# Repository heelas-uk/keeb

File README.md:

# Keeb
A project for hackclub ~keeb~ forge YSWS 

It's a stenography keyboard. It is custom because my keyboard doesn't have proper n key roll over. This is also my first time in cad and kicad so its bad. 

This is the schematic of what I have made. 

# How to make

1. Acquire the pcb and 3d model of the case in pla (realistically you should use the one with no top since the top plate isn't essential and a pain to print).

3. Acquire other components per bill of materials

4. Soldering fun. Attach the components with lead free solder.

5. Check it works... kinda really important before you put it in a case

6. Build the case with self tapping screws so there is good stability.

7. Flash the firmware by holding bootsel and drag and drop

8. Install plover HID on you device and plugin via usb

9. It should now work. Yay!

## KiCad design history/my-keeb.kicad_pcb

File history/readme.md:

I have quite litterally just uploaded the files as amd when they were added to the histpry repo in kicad

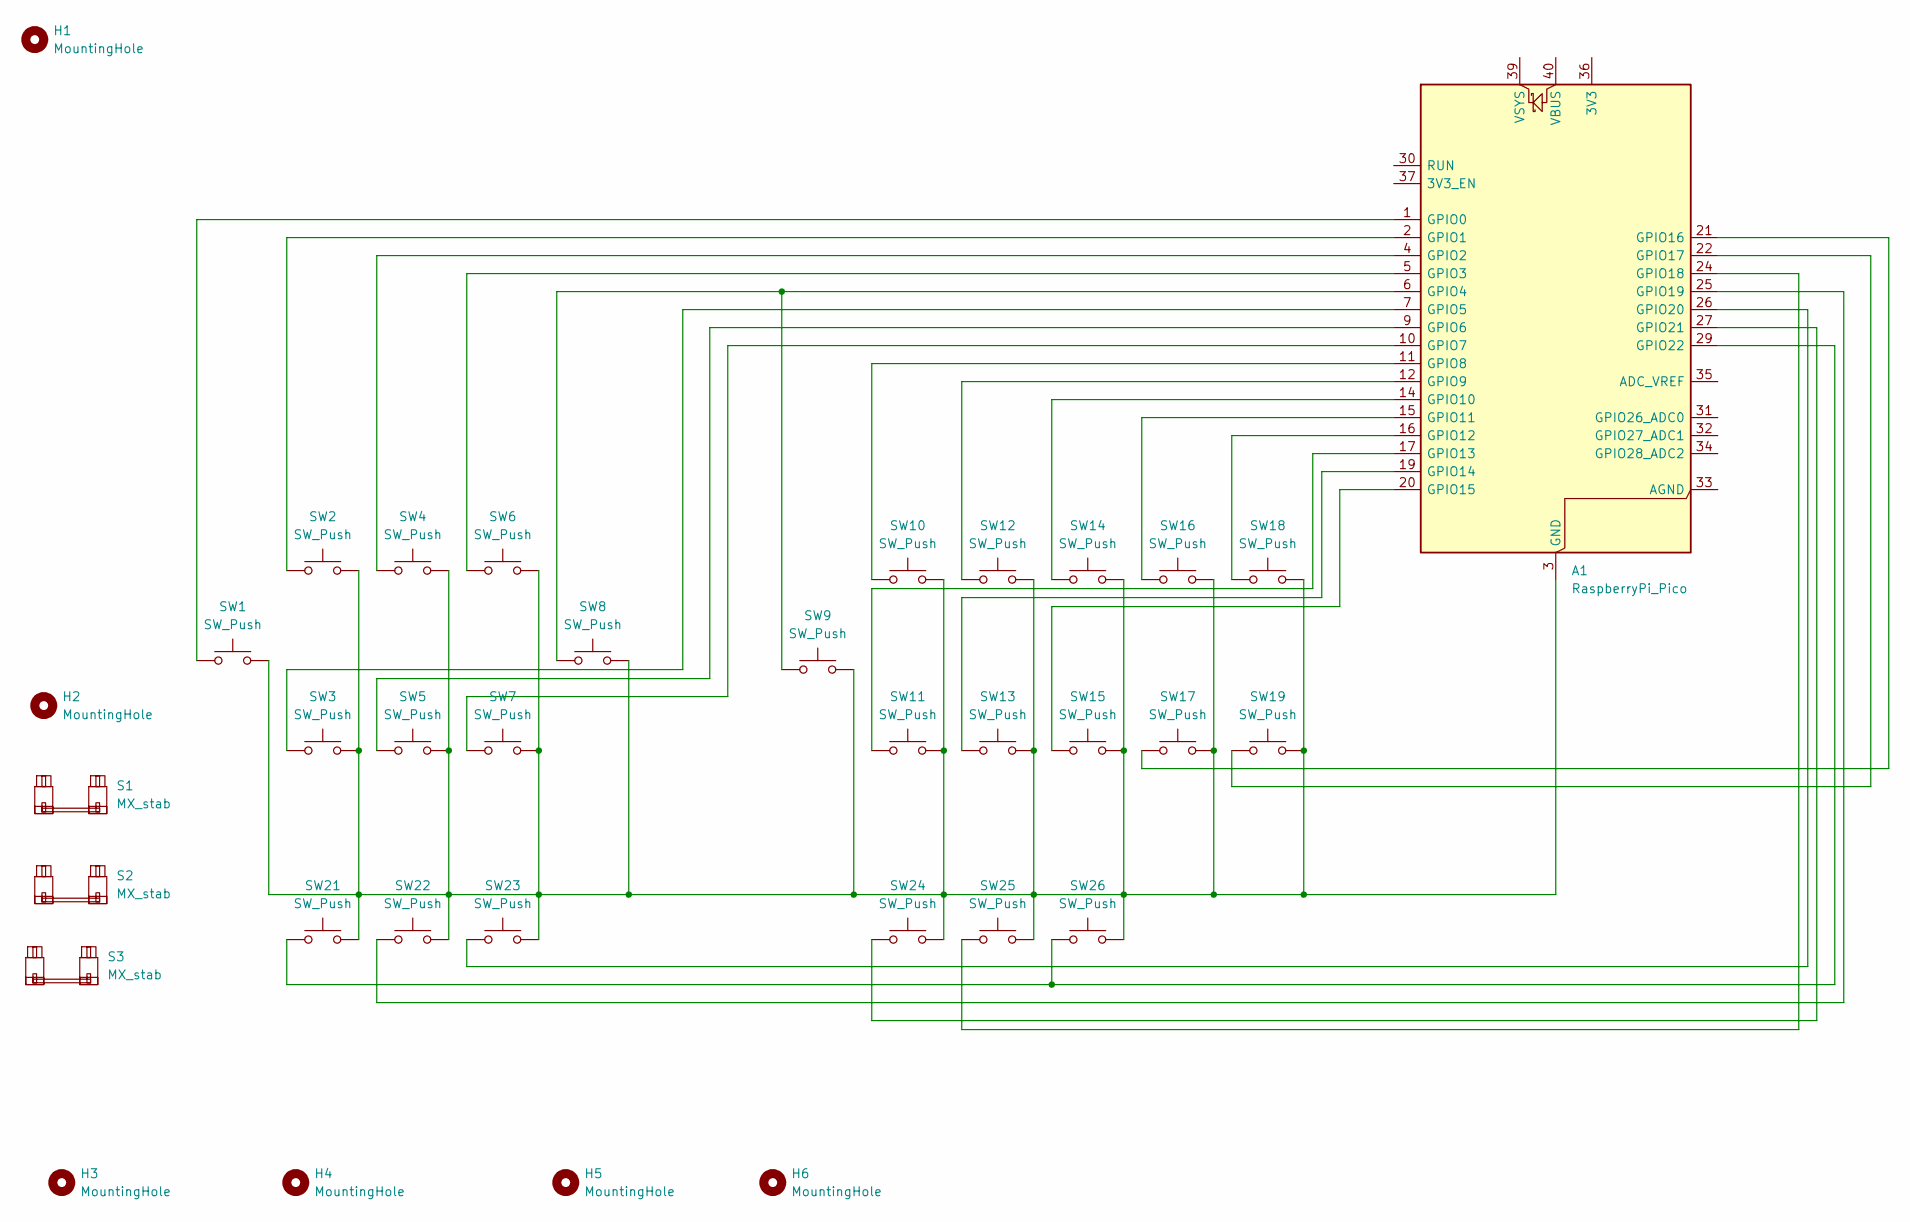
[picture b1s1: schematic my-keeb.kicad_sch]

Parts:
A1: RaspberryPi_Pico; RaspberryPi_Pico_Common_THT
H1, H2, H3, H4, H5, H6: MountingHole; MountingHole_3.2mm_M3
S1, S2, S3: MX_stab; STAB_MX_P_2u
SW1, SW2, SW3, SW4, SW5, SW6, SW7, SW8, SW9, SW10, SW11, SW12, SW13, SW14, SW15, SW16, SW17, SW18, SW19, SW21, SW22, SW23, SW24, SW25, SW26: SW_Push; SW_MX_1u

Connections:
unnamed: A1.3 (GND), A1.8 (GND), A1.13 (GND), A1.18 (GND), A1.23 (GND), A1.28 (GND), A1.38 (GND), SW1.2, SW2.2, SW3.2, SW4.2, SW5.2, SW6.2, SW7.2, SW8.2, SW9.2, SW10.2, SW11.2, SW12.2, SW13.2, SW14.2, SW15.2, SW16.2, SW17.2, SW18.2, SW19.2, SW21.2, SW22.2, SW23.2, SW24.2, SW25.2, SW26.2
unnamed: A1.1 (GPIO0), SW1.1
unnamed: A1.2 (GPIO1), SW2.1
unnamed: A1.4 (GPIO2), SW4.1
unnamed: A1.5 (GPIO3), SW6.1
unnamed: A1.6 (GPIO4), SW8.1, SW9.1
unnamed: A1.7 (GPIO5), SW3.1
unnamed: A1.9 (GPIO6), SW5.1
unnamed: A1.10 (GPIO7), SW7.1
unnamed: A1.11 (GPIO8), SW10.1
unnamed: A1.12 (GPIO9), SW12.1
unnamed: A1.14 (GPIO10), SW14.1
unnamed: A1.15 (GPIO11), SW16.1
unnamed: A1.16 (GPIO12), SW18.1
unnamed: A1.17 (GPIO13), SW11.1
unnamed: A1.19 (GPIO14), SW13.1
unnamed: A1.20 (GPIO15), SW15.1
unnamed: A1.21 (GPIO16), SW17.1
unnamed: A1.22 (GPIO17), SW19.1
unnamed: A1.24 (GPIO18), SW25.1
unnamed: A1.25 (GPIO19), SW22.1
unnamed: A1.26 (GPIO20), SW23.1
unnamed: A1.27 (GPIO21), SW24.1
unnamed: A1.29 (GPIO22), SW21.1, SW26.1

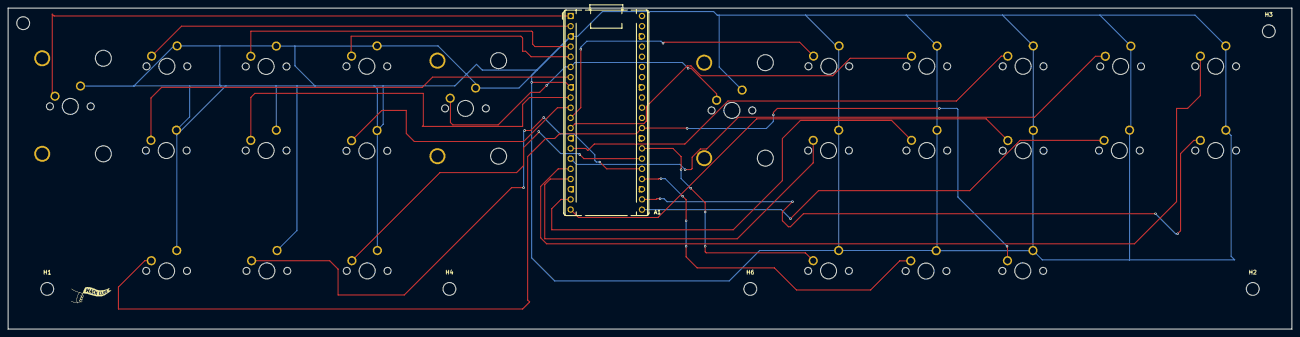
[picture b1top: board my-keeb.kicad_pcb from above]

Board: 2 copper layers, 320.0 x 80.0 mm, 35 parts (0 on the bottom side), 24 nets.

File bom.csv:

Reference,Qty,Component ,Cost GBP (£),Reason,Supplier
A1,1,RaspberryPi_Pico_WH,6.7,"The Pico W is by far the most versatile, microcontroller to be used. Ideally I would like to use the orpheus pico but I can't see that as an opiton so this will have to do. I decided on the with pins as it saved 10p and reduced the risk of  my soldering invertibly messing somthing up. The descion for the W model was that I could use it with bluetooth attached to plover if it is a normal kebaord as opposed to the plover HID protocol. ",https://thepihut.com/products/raspberry-pi-pico-w?variant=41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
"S1,S2,S3",3,MX_stab,4.59,It's the seemingly cheapest I could get with a lcear desciption and I have free amazon prime so not a mellina of shipping ,https://www.amazon.co.uk/Hundnsney-Mounted-Stabilizer-Mechan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
"SW1,SW2,SW3,SW4,SW5,SW6,SW7,SW8,SW9,SW10,SW11,SW12,SW13,SW14,SW15,SW16,SW17,SW18,SW19,SW21,SW22,SW23,SW24,SW25,SW26",25,MX style switch - Silent Peach V3 linear light switch pack of 30,1.29,Its a Steno keyboard so I need the lightest silent switch I can since I will be pressing up to 10 keys at a time and RSI doesn't sound fun ,https://www.aliexpress.com/item/1005007459638140.html?spm=a2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
N/A,22,MX/DSA style keycaps (1u) ,0.84,Ideally I want DSA keycaps so theyre the same height and theyre the same keycaps and match my 2u keycaps ,https://www.aliexpress.com/item/1005008827240220.html?spm=a2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
N/A,3,MX/DSA style keycaps (2u),£3.64,It is very difficult to find 2u keycaps or a pack where there is more than 2 this is that and matches my 1u keycaps,https://www.aliexpress.com/item/1005008827240220.html?spm=a2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
PCB,1,PCB - custom ,0,Its quite important - exchnage rates is 14.77USD after coupon and using the app inc current shipping ,https://jlcpcb.com/
3d print ,1,PCB case - (no plate since its not that critical for my use case),29.75,"This is a number that is unrealisitc since if you brought the pcb and 3dp at the same time it would cost 29.75, if it was prin leigon I would have to wait and see",
,,Total:,46.81,,
